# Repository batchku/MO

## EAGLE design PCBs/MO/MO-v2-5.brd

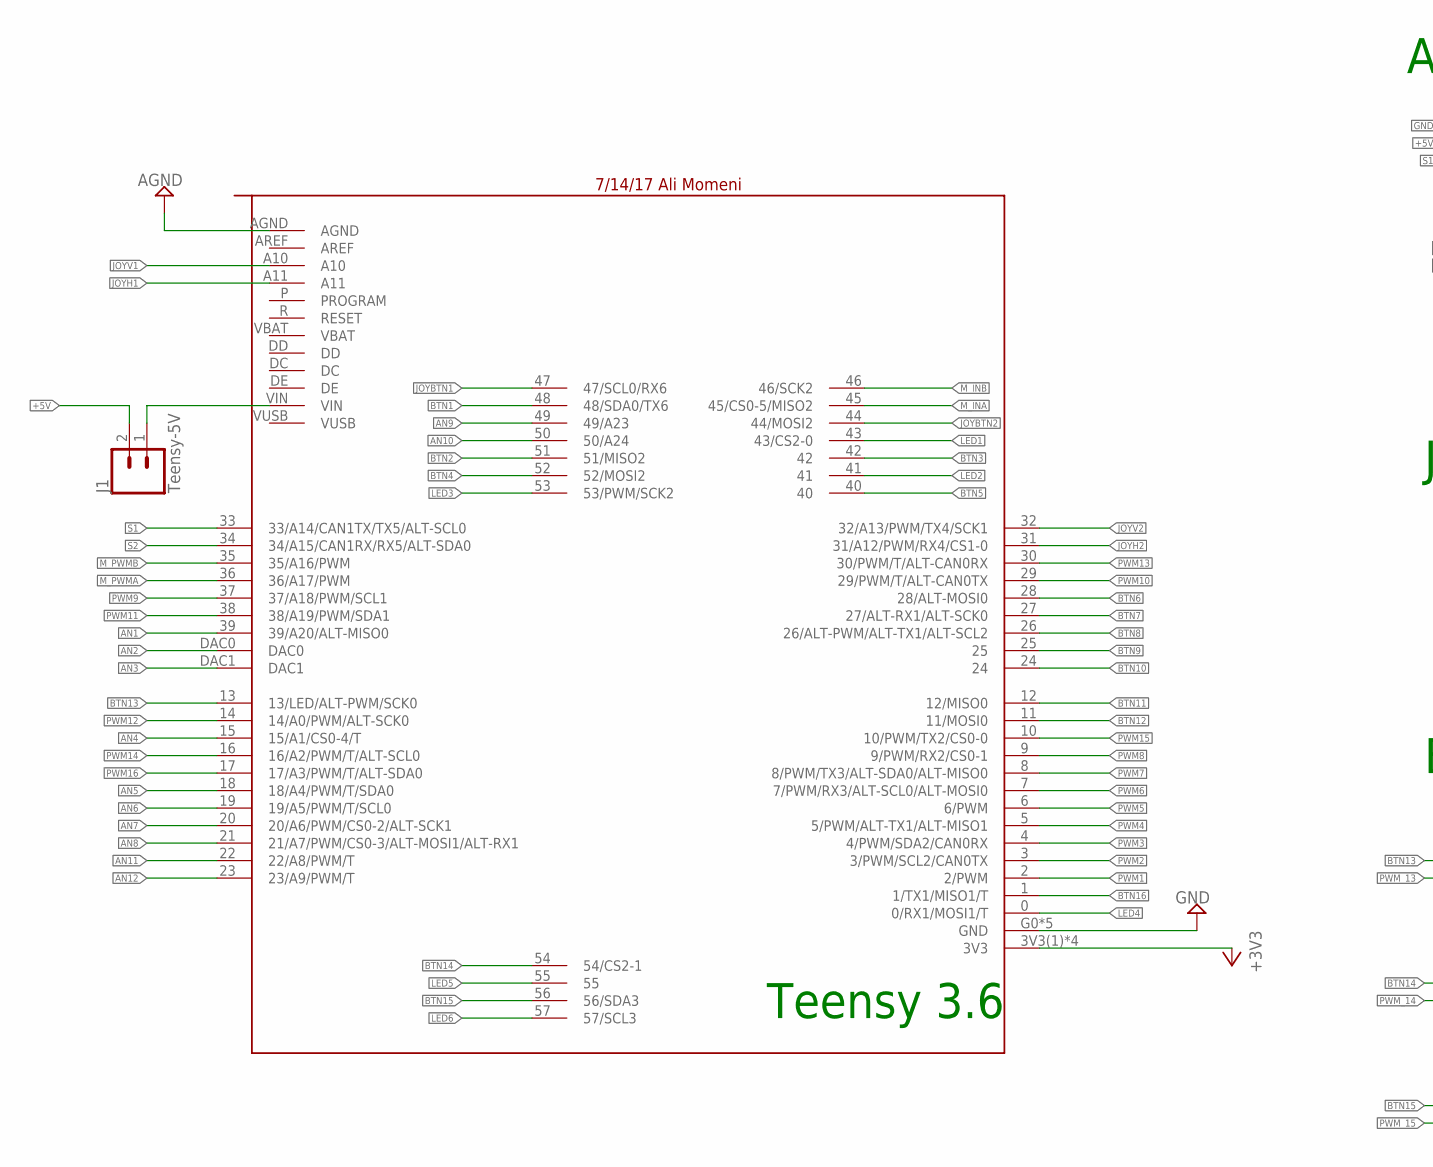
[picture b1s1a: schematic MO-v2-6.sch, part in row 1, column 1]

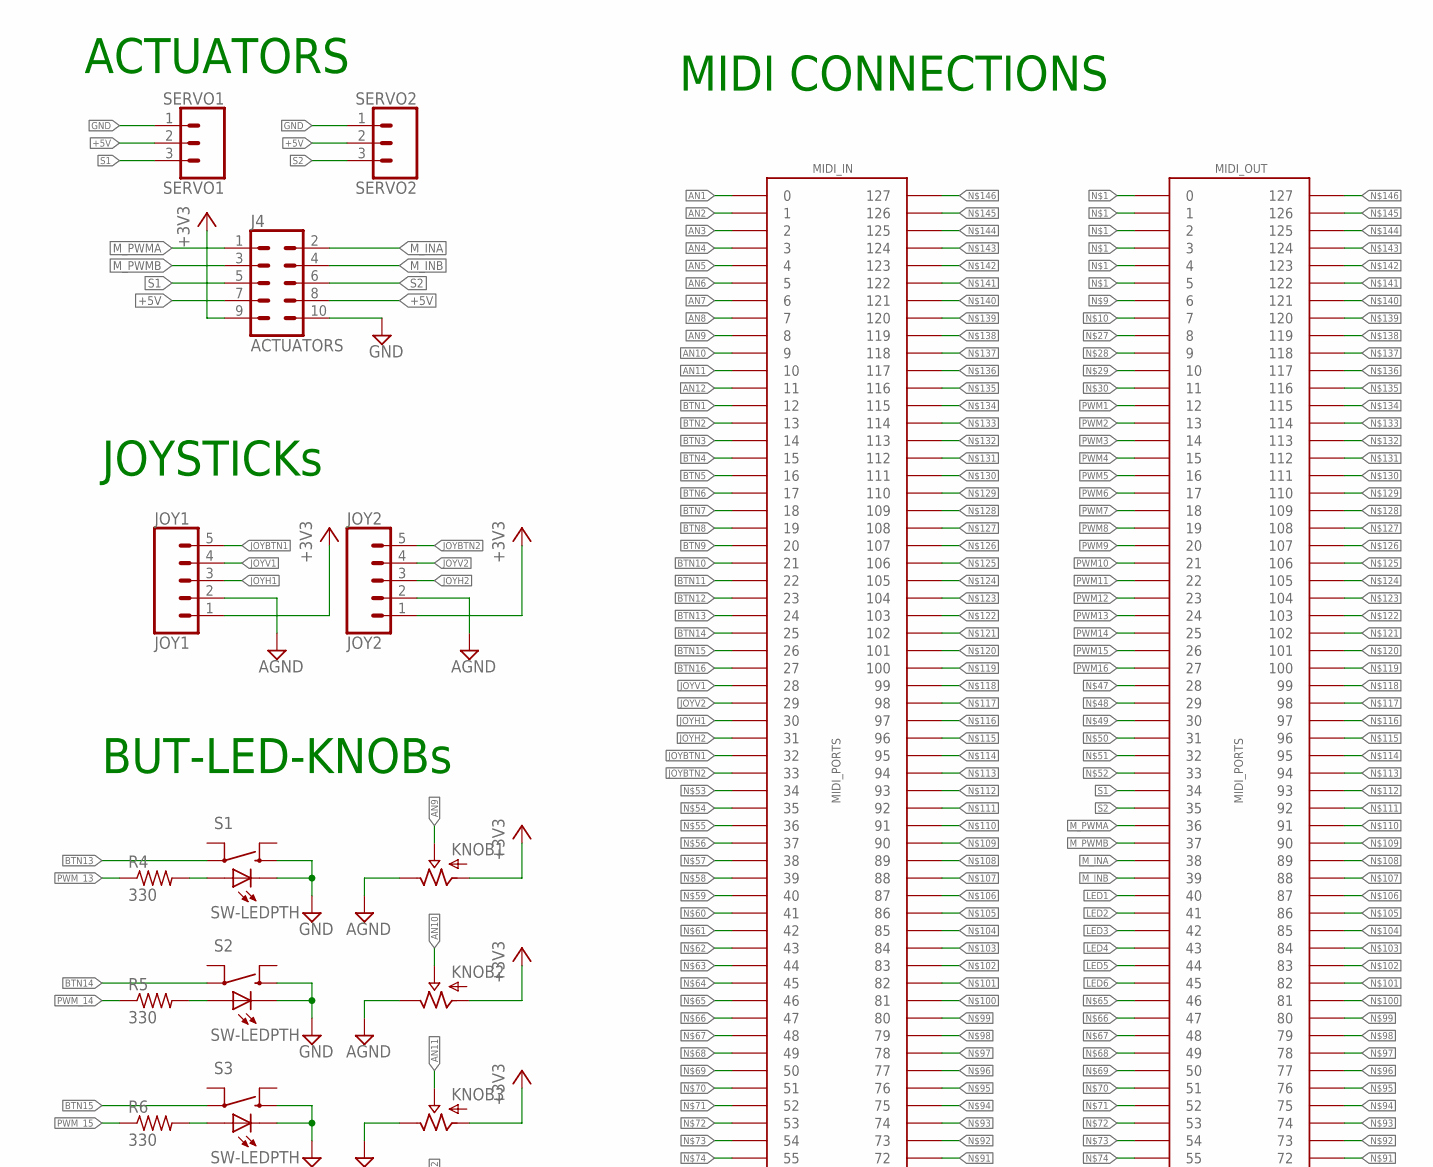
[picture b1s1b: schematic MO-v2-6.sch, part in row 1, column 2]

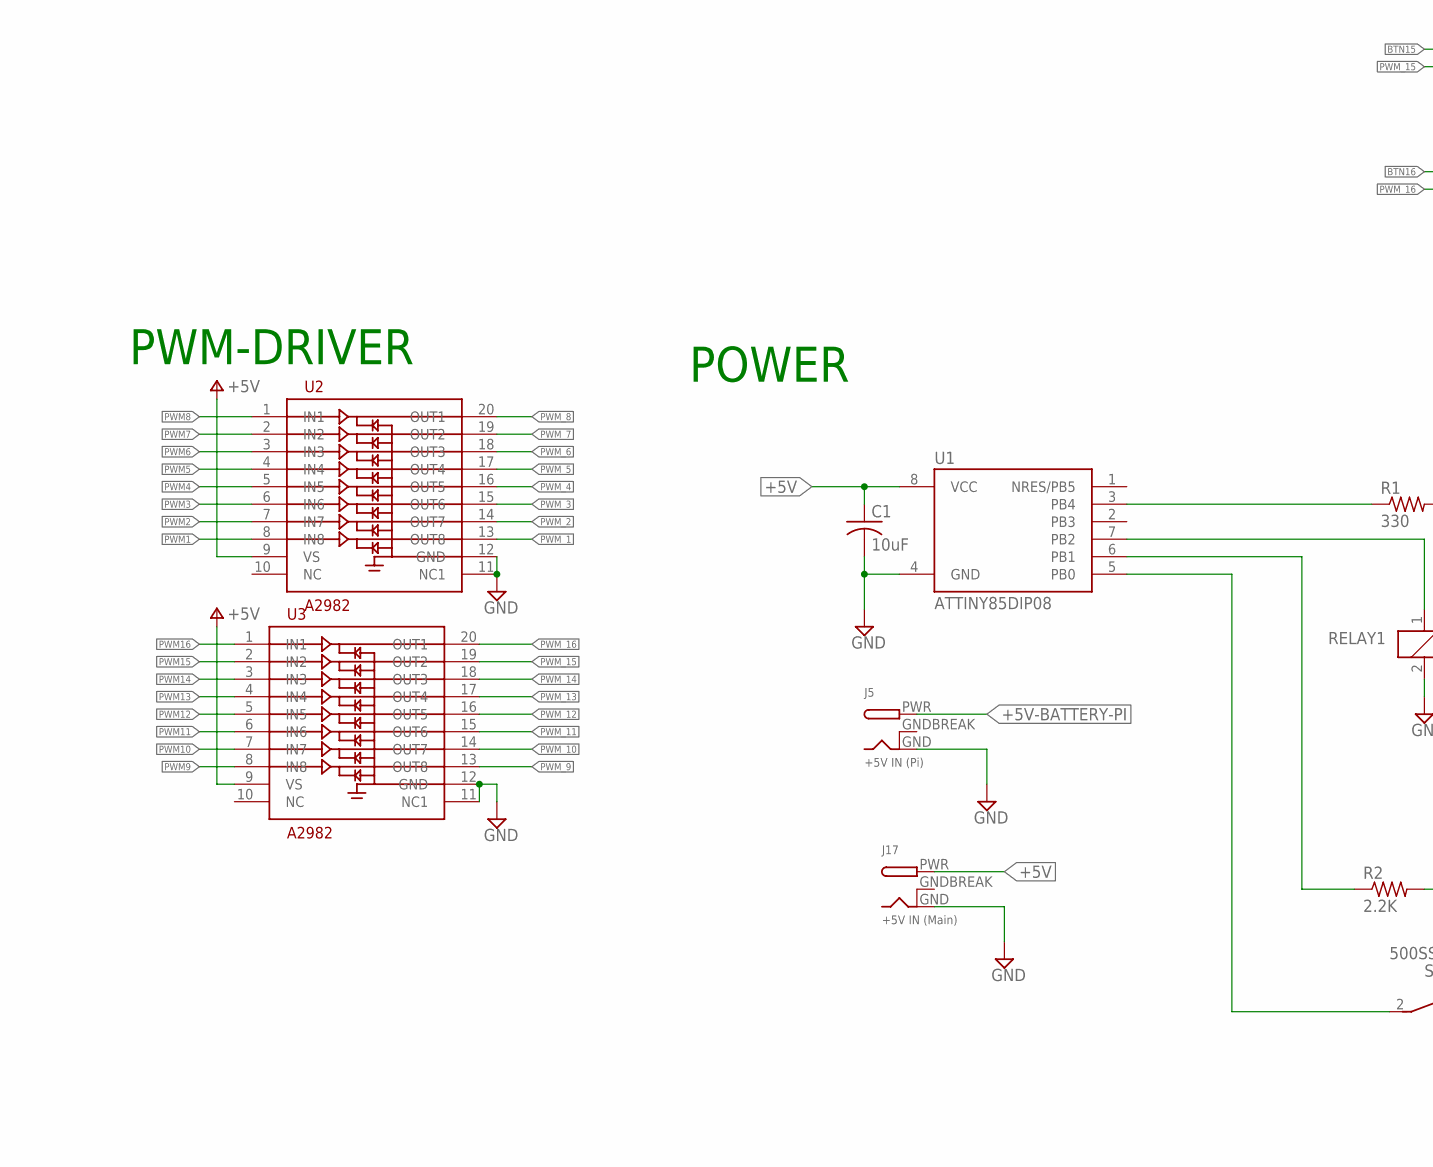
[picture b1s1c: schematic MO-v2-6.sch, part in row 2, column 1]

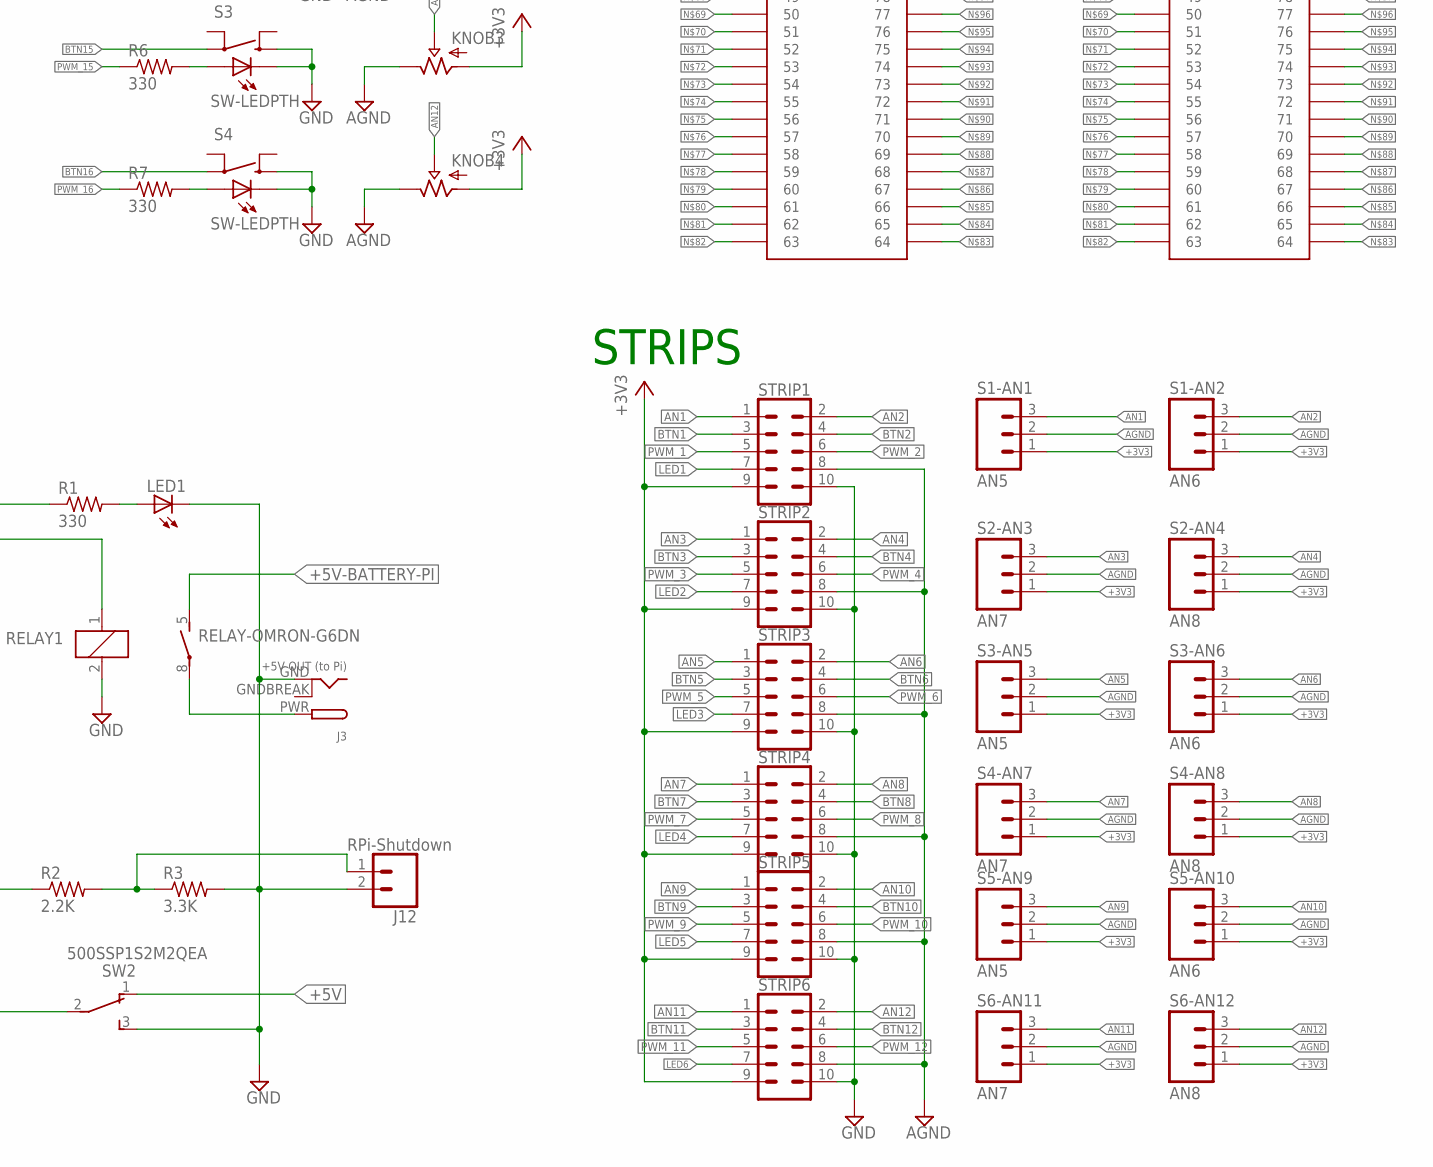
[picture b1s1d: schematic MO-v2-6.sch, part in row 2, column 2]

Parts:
C1: 10uF; C050-024X044
J1: Teensy-5V; 1X02_LOCK
J3: +5V OUT (to Pi); DCJACK_2MM_PTH
J4: ACTUATORS; 2X5-SHROUDED_LOCK
J5: +5V IN (Pi); DCJACK_2MM_PTH
J12: RPi-Shutdown; 1X02_LOCK
J17: +5V IN (Main); DCJACK_2MM_PTH
JOY1: JOY1; 1X05_LOCK
JOY2: JOY2; 1X05_LOCK
KNOB1, KNOB2, KNOB3, KNOB4: POTALPHA_RD901; POT_ALPHA_RD901F-40-(L)R1
LED1: LED3MM
R1, R4, R5, R6, R7: 330; 0204/7
R2: 2.2K; 0204/7
R3: 3.3K; 0204/7
RELAY1: RELAY-OMRON-G6DN; G6DN-1A
S1, S2, S3, S4: SW-LEDPTH; SWITCH_TR2-MOMENTARY-LED
S1-AN1, S3-AN5, S5-AN9: AN5; 1X03_LOCK
S1-AN2, S3-AN6, S5-AN10: AN6; 1X03_LOCK
S2-AN3, S4-AN7, S6-AN11: AN7; 1X03_LOCK
S2-AN4, S4-AN8, S6-AN12: AN8; 1X03_LOCK
SERVO1: SERVO1; 1X03_LOCK@1
SERVO2: SERVO2; 1X03_LOCK@1
STRIP1, STRIP2, STRIP3, STRIP4, STRIP5, STRIP6: CONN_05X2SHD_LOCK; 2X5-SHROUDED_LOCK
SW2: 500SSP1S2M2QEA; SWITCH_SPDT_500SSP1S2M2QEA
TEENSY: TEENSY3_6-ALI_NO-USB-HOST; TEENSY3-6_NO-USB-HOST
U1: ATTINY85DIP08; DIP08
U2, U3: A2982; SOIC20

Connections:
+3V3: J4.9, JOY1.1, JOY2.1, KNOB1.1 (IN), KNOB2.1 (IN), KNOB3.1 (IN), KNOB4.1 (IN), S1-AN1.1, S1-AN2.1, S2-AN3.1, S2-AN4.1, S3-AN5.1, S3-AN6.1, S4-AN7.1, S4-AN8.1, S5-AN9.1, S5-AN10.1, S6-AN11.1, S6-AN12.1, STRIP1.9, STRIP2.9, STRIP3.9, STRIP4.9, STRIP5.9, STRIP6.9, TEENSY.3V3(1) (3V3), TEENSY.3V3(2) (3V3), TEENSY.3V3(3) (3V3), TEENSY.3V3(4) (3V3); also elsewhere on the board
+5V: C1.1, J1.2, J4.7, J4.8, J17.PWR, SERVO1.2, SERVO2.2, SW2.1, U1.8 (VCC), U2.9 (VS), U3.9 (VS); also elsewhere on the board
+5V-BATTERY-PI: J5.PWR, RELAY1.5
AGND: JOY1.2, JOY2.2, KNOB1.3 (OUT), KNOB2.3 (OUT), KNOB3.3 (OUT), KNOB4.3 (OUT), S1-AN1.2, S1-AN2.2, S2-AN3.2, S2-AN4.2, S3-AN5.2, S3-AN6.2, S4-AN7.2, S4-AN8.2, S5-AN9.2, S5-AN10.2, S6-AN11.2, S6-AN12.2, STRIP1.8, STRIP2.8, STRIP3.8, STRIP4.8, STRIP5.8, STRIP6.8, TEENSY.AGND; also elsewhere on the board
AN1: S1-AN1.3, STRIP1.1, TEENSY.39 (39/A20/ALT-MISO0)
AN2: S1-AN2.3, STRIP1.2, TEENSY.DAC0
AN3: S2-AN3.3, STRIP2.1, TEENSY.DAC1
AN4: S2-AN4.3, STRIP2.2, TEENSY.15 (15/A1/CS0-4/T)
AN5: S3-AN5.3, STRIP3.1, TEENSY.18 (18/A4/PWM/T/SDA0)
AN6: S3-AN6.3, STRIP3.2, TEENSY.19 (19/A5/PWM/T/SCL0)
AN7: S4-AN7.3, STRIP4.1, TEENSY.20 (20/A6/PWM/CS0-2/ALT-SCK1)
AN8: S4-AN8.3, STRIP4.2, TEENSY.21 (21/A7/PWM/CS0-3/ALT-MOSI1/ALT-RX1)
AN9: KNOB1.2 (WIPER), S5-AN9.3, STRIP5.1, TEENSY.49 (49/A23); also elsewhere on the board
AN10: KNOB2.2 (WIPER), S5-AN10.3, STRIP5.2, TEENSY.50 (50/A24); also elsewhere on the board
AN11: KNOB3.2 (WIPER), S6-AN11.3, STRIP6.1, TEENSY.22 (22/A8/PWM/T); also elsewhere on the board
AN12: KNOB4.2 (WIPER), S6-AN12.3, STRIP6.2, TEENSY.23 (23/A9/PWM/T); also elsewhere on the board
BTN1: STRIP1.3, TEENSY.48 (48/SDA0/TX6)
BTN2: STRIP1.4, TEENSY.51 (51/MISO2)
BTN3: STRIP2.3, TEENSY.42
BTN4: STRIP2.4, TEENSY.52 (52/MOSI2)
BTN5: STRIP3.3, TEENSY.40
BTN6: STRIP3.4, TEENSY.28 (28/ALT-MOSI0)
BTN7: STRIP4.3, TEENSY.27 (27/ALT-RX1/ALT-SCK0)
BTN8: STRIP4.4, TEENSY.26 (26/ALT-PWM/ALT-TX1/ALT-SCL2)
BTN9: STRIP5.3, TEENSY.25
BTN10: STRIP5.4, TEENSY.24
BTN11: STRIP6.3, TEENSY.12 (12/MISO0)
BTN12: STRIP6.4, TEENSY.11 (11/MOSI0)
BTN13: S1.3, TEENSY.13 (13/LED/ALT-PWM/SCK0)
BTN14: S2.3, TEENSY.54 (54/CS2-1)
BTN15: S3.3, TEENSY.56 (56/SDA3)
BTN16: S4.3, TEENSY.1 (1/TX1/MISO1/T)
GND: C1.2, J3.GND, J4.10, J5.GND, J12.2, J17.GND, LED1.K (C), R3.2, RELAY1.2, S1.1, S1.C, S2.1, S2.C, S3.1, S3.C, S4.1, S4.C, SERVO1.1, SERVO2.1, STRIP1.10, STRIP2.10, STRIP3.10, STRIP4.10, STRIP5.10, STRIP6.10, SW2.3, TEENSY.G0 (GND), TEENSY.G1 (GND), TEENSY.G2 (GND), TEENSY.G3 (GND), TEENSY.G6 (GND), U1.4 (GND), U2.11 (NC1), U2.12 (GND), U3.11 (NC1), U3.12 (GND); also elsewhere on the board
GNDBREAK: J3.GNDBREAK, J5.GNDBREAK, J17.GNDBREAK
JOYB1: JOY1.5, TEENSY.47 (47/SCL0/RX6)
JOYB2: JOY2.5, TEENSY.44 (44/MOSI2)
JOYH1: JOY1.3, TEENSY.A11
JOYH2: JOY2.3, TEENSY.31 (31/A12/PWM/RX4/CS1-0)
JOYV1: JOY1.4, TEENSY.A10
JOYV2: JOY2.4, TEENSY.32 (32/A13/PWM/TX4/SCK1)
LED1: STRIP1.7, TEENSY.43 (43/CS2-0)
LED2: STRIP2.7, TEENSY.41
LED3: STRIP3.7, TEENSY.53 (53/PWM/SCK2)
LED4: STRIP4.7, TEENSY.0 (0/RX1/MOSI1/T)
LED5: STRIP5.7, TEENSY.55
LED6: STRIP6.7, TEENSY.57 (57/SCL3)
M_INA: J4.2, TEENSY.45 (45/CS0-5/MISO2)
M_INB: J4.4, TEENSY.46 (46/SCK2)
M_PWMA: J4.1, TEENSY.36 (36/A17/PWM)
M_PWMB: J4.3, TEENSY.35 (35/A16/PWM)
unnamed: LED1.A, R1.2
unnamed: R4.2, S1.A
unnamed: R5.2, S2.A
unnamed: J12.1, R2.2, R3.1
unnamed: R6.2, S3.A
unnamed: J1.1, TEENSY.VIN
unnamed: R7.2, S4.A
PI-REST: R2.1, U1.6 (PB1)
PWM1: TEENSY.2 (2/PWM), U2.8 (IN8)
PWM2: TEENSY.3 (3/PWM/SCL2/CAN0TX), U2.7 (IN7)
PWM3: TEENSY.4 (4/PWM/SDA2/CAN0RX), U2.6 (IN6)
PWM4: TEENSY.5 (5/PWM/ALT-TX1/ALT-MISO1), U2.5 (IN5)
PWM5: TEENSY.6 (6/PWM), U2.4 (IN4)
PWM6: TEENSY.7 (7/PWM/RX3/ALT-SCL0/ALT-MOSI0), U2.3 (IN3)
PWM7: TEENSY.8 (8/PWM/TX3/ALT-SDA0/ALT-MISO0), U2.2 (IN2)
PWM8: TEENSY.9 (9/PWM/RX2/CS0-1), U2.1 (IN1)
PWM9: TEENSY.37 (37/A18/PWM/SCL1), U3.8 (IN8); also elsewhere on the board
PWM10: TEENSY.29 (29/PWM/T/ALT-CAN0TX), U3.7 (IN7); also elsewhere on the board
PWM11: TEENSY.38 (38/A19/PWM/SDA1), U3.6 (IN6); also elsewhere on the board
PWM12: TEENSY.14 (14/A0/PWM/ALT-SCK0), U3.5 (IN5); also elsewhere on the board
PWM13: TEENSY.30 (30/PWM/T/ALT-CAN0RX), U3.4 (IN4); also elsewhere on the board
PWM14: TEENSY.16 (16/A2/PWM/T/ALT-SCL0), U3.3 (IN3); also elsewhere on the board
PWM15: TEENSY.10 (10/PWM/TX2/CS0-0), U3.2 (IN2); also elsewhere on the board
PWM16: TEENSY.17 (17/A3/PWM/T/ALT-SDA0), U3.1 (IN1); also elsewhere on the board
PWM_1: STRIP1.5, U2.13 (OUT8)
PWM_2: STRIP1.6, U2.14 (OUT7)
PWM_3: STRIP2.5, U2.15 (OUT6)
PWM_4: STRIP2.6, U2.16 (OUT5)
PWM_5: STRIP3.5, U2.17 (OUT4)
PWM_6: STRIP3.6, U2.18 (OUT3)
PWM_7: STRIP4.5, U2.19 (OUT2)
PWM_8: STRIP4.6, U2.20 (OUT1)
PWM_9: STRIP5.5, U3.13 (OUT8); also elsewhere on the board
PWM_10: STRIP5.6, U3.14 (OUT7); also elsewhere on the board
PWM_11: STRIP6.5, U3.15 (OUT6); also elsewhere on the board
PWM_12: STRIP6.6, U3.16 (OUT5); also elsewhere on the board
PWM_13: R4.1, U3.17 (OUT4); also elsewhere on the board
PWM_14: R5.1, U3.18 (OUT3); also elsewhere on the board
PWM_15: R6.1, U3.19 (OUT2); also elsewhere on the board
PWM_16: R7.1, U3.20 (OUT1); also elsewhere on the board
RELAY-PWR: J3.PWR, RELAY1.8
S1: J4.5, SERVO1.3, TEENSY.33 (33/A14/CAN1TX/TX5/ALT-SCL0)
S2: J4.6, SERVO2.3, TEENSY.34 (34/A15/CAN1RX/RX5/ALT-SDA0)
TINY_LED: R1.1, U1.3 (PB4)
TINY_RELAY: RELAY1.1, U1.7 (PB2)
TINY_SWITCH: SW2.2, U1.5 (PB0)

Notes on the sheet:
BUT-LED-KNOBs
JOYSTICKs
PWM-DRIVER
STRIPS
ACTUATORS
POWER
Teensy 3.6
MIDI CONNECTIONS

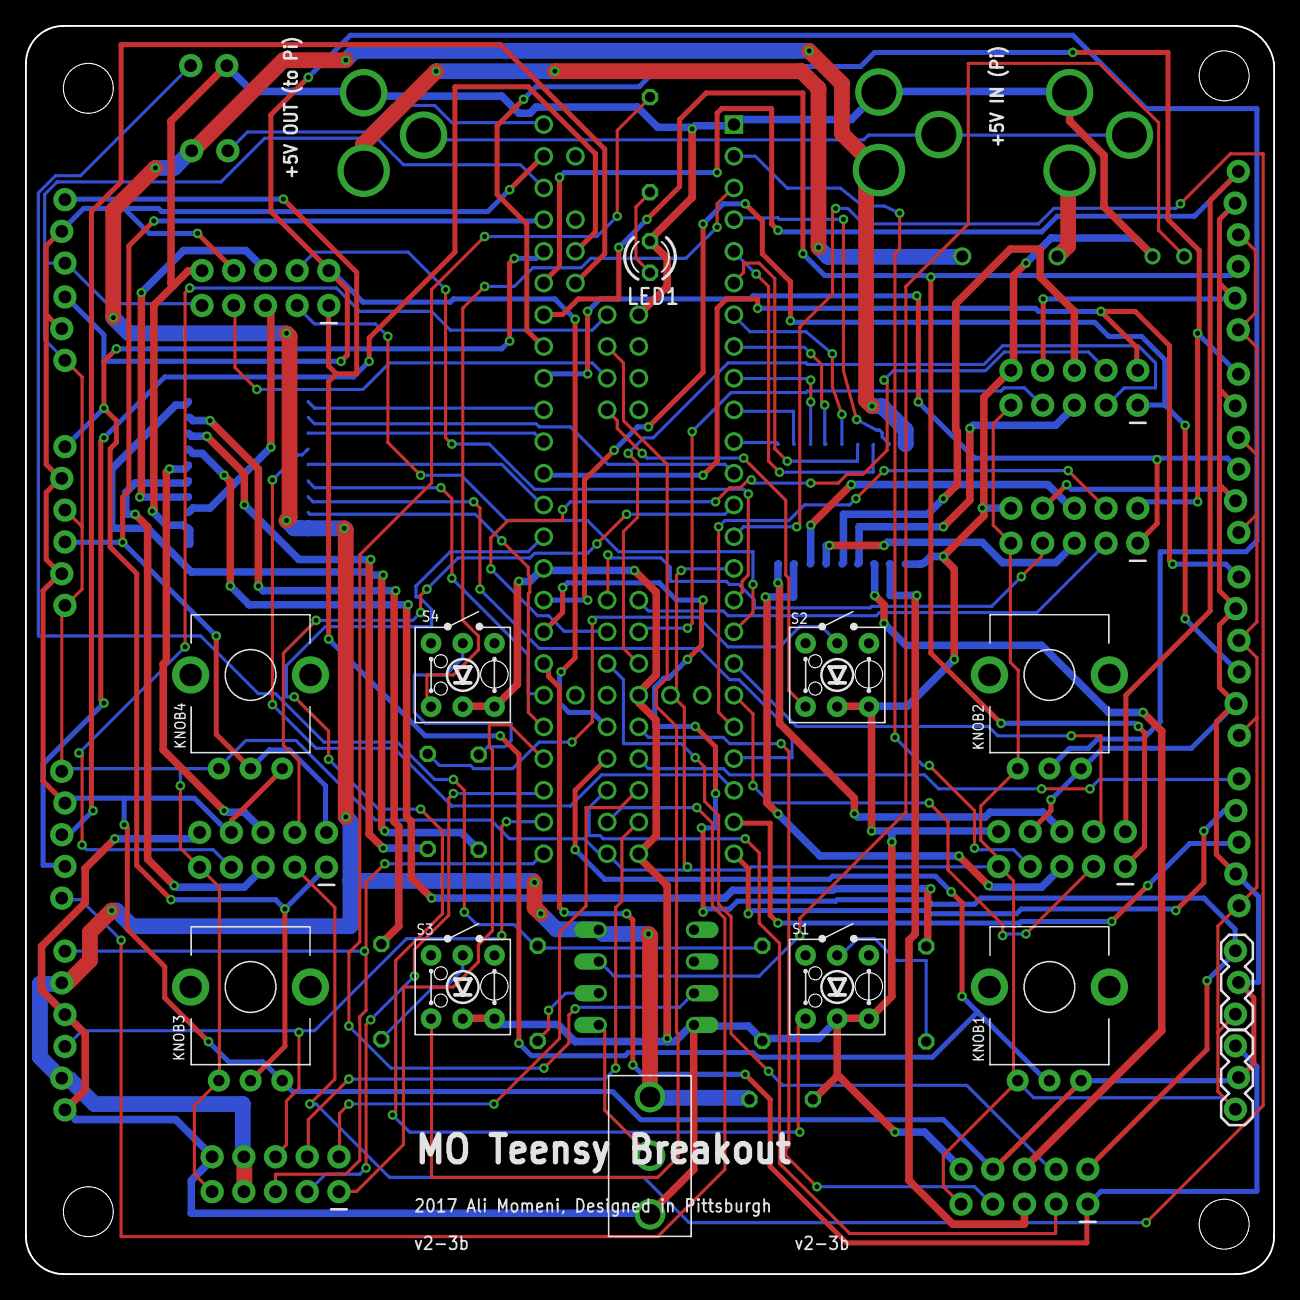
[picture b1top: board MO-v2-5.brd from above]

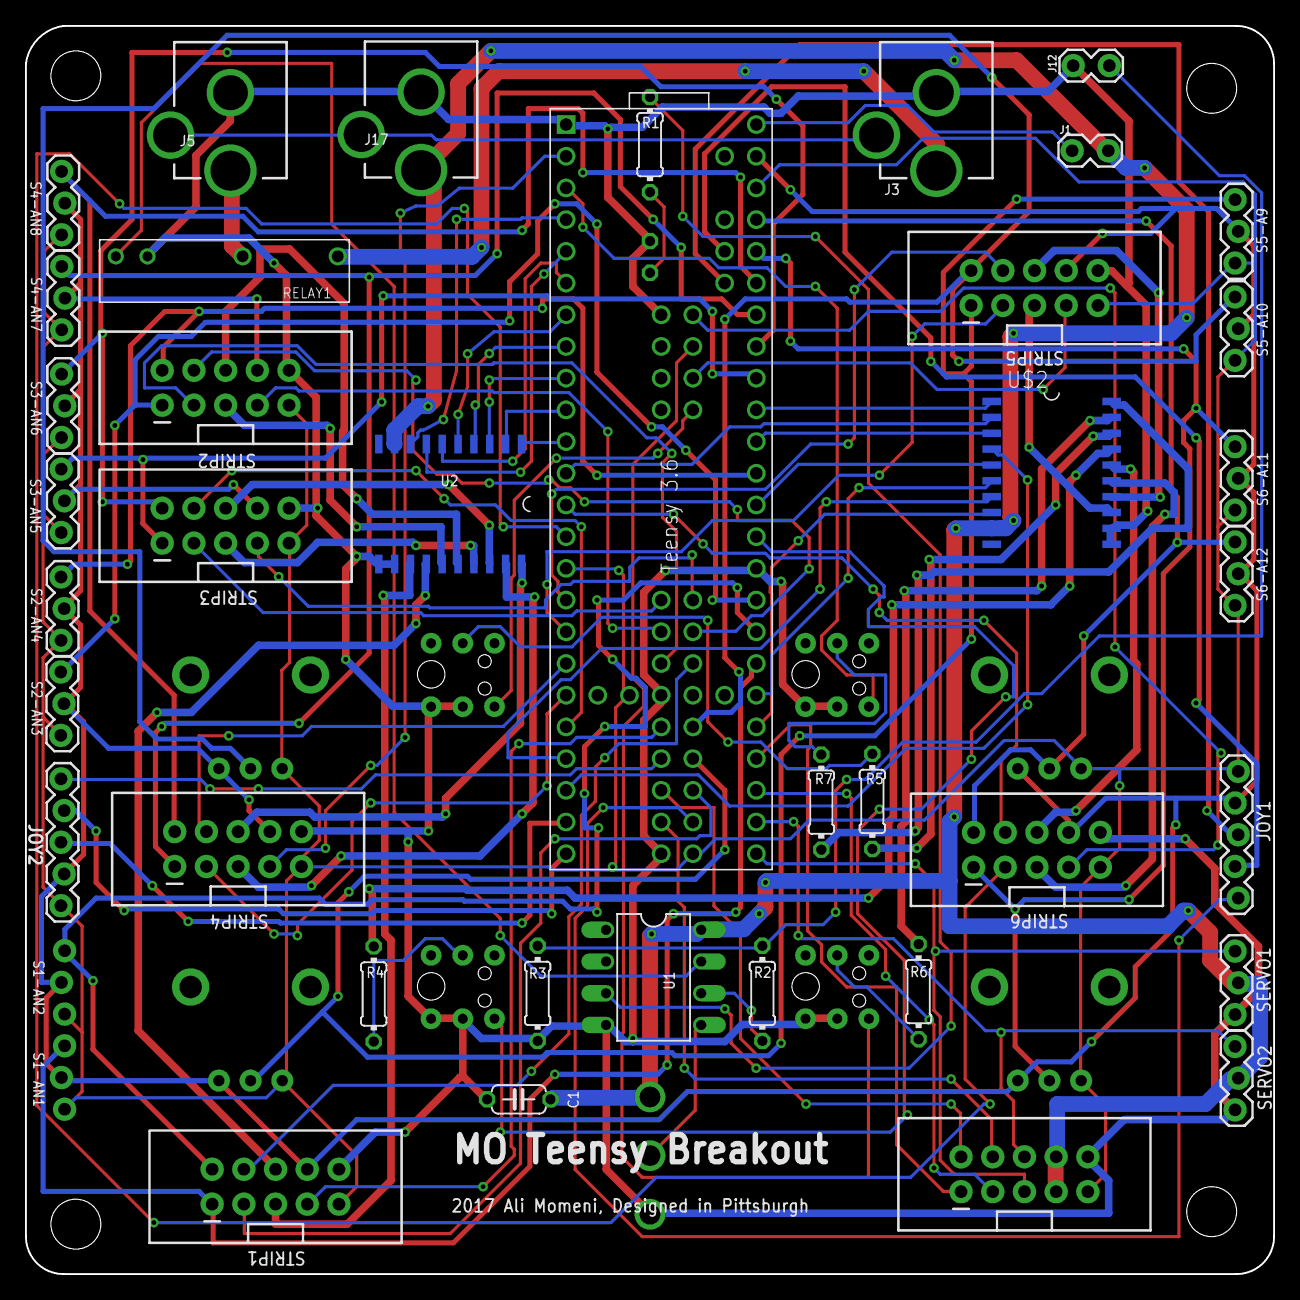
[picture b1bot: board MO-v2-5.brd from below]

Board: 2 copper layers, 100.0 x 100.0 mm, 51 parts (39 on the bottom side), 96 nets.

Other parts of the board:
S5-A9: AN5; 1X03_LOCK
S5-A10: AN6; 1X03_LOCK
S6-A11: AN7; 1X03_LOCK
S6-A12: AN8; 1X03_LOCK
U$2: A2982; SOIC20

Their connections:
+3V3: S5-A9.1, S5-A10.1, S6-A11.1, S6-A12.1; also elsewhere on the board
+5V: U$2.9; also elsewhere on the board
AGND: S5-A9.2, S5-A10.2, S6-A11.2, S6-A12.2; also elsewhere on the board
AN9: S5-A9.3; also elsewhere on the board
AN10: S5-A10.3; also elsewhere on the board
AN11: S6-A11.3; also elsewhere on the board
AN12: S6-A12.3; also elsewhere on the board
GND: U$2.11, U$2.12; also elsewhere on the board
PWM9: U$2.8; also elsewhere on the board
PWM10: U$2.7; also elsewhere on the board
PWM11: U$2.6; also elsewhere on the board
PWM12: U$2.5; also elsewhere on the board
PWM13: U$2.4; also elsewhere on the board
PWM14: U$2.3; also elsewhere on the board
PWM15: U$2.2; also elsewhere on the board
PWM16: U$2.1; also elsewhere on the board
PWM_9: U$2.13; also elsewhere on the board
PWM_10: U$2.14; also elsewhere on the board
PWM_11: U$2.15; also elsewhere on the board
PWM_12: U$2.16; also elsewhere on the board
PWM_13: U$2.17; also elsewhere on the board
PWM_14: U$2.18; also elsewhere on the board
PWM_15: U$2.19; also elsewhere on the board
PWM_16: U$2.20; also elsewhere on the board

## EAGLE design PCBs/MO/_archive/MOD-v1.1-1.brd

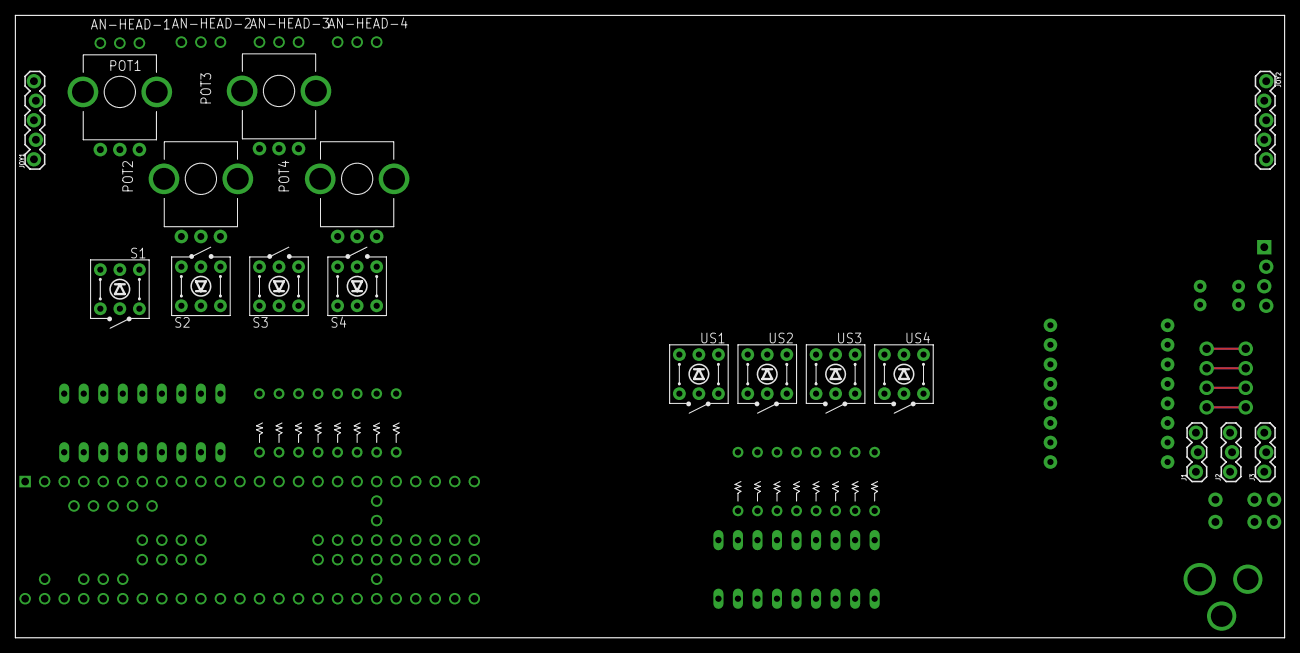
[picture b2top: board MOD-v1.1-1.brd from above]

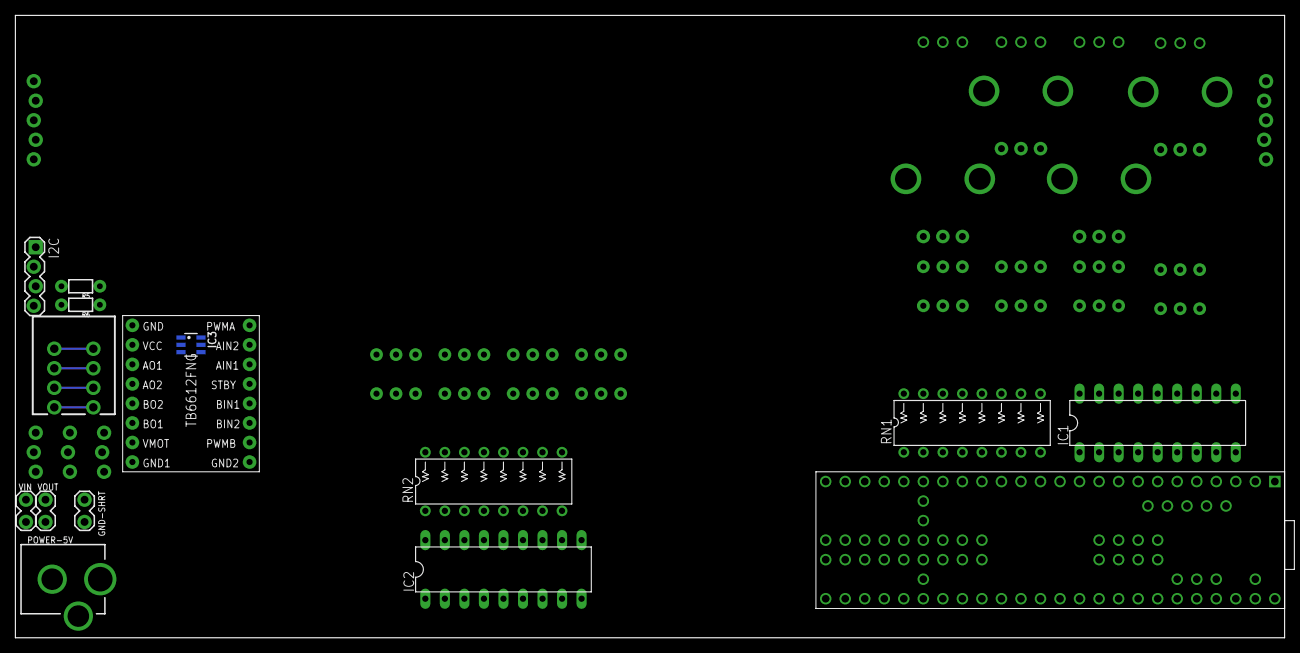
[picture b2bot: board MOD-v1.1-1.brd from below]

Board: 2 copper layers, 165.1 x 81.0 mm, 36 parts (15 on the bottom side), 80 nets, no tracks yet.

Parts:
AN-HEAD-1, AN-HEAD-2, AN-HEAD-3, AN-HEAD-4: 1X03_NO_SILK
GND-SHRT: 1X02_LOCK
I2C: 1X04_LOCK
IC1, IC2: ULN2803; DIL18
IC3: SN74LVC2G04DBV; SOT23-6
J1: SERVO 1; 1X03_LOCK@1
J2: SERVO 2; 1X03_LOCK@1
J3: SERVO 3; 1X03_LOCK@1
JOY1, JOY2: 1X05_LOCK
MOTORS1: SPRINGTERMINAL-2.54MM-4
POT1, POT2, POT3, POT4: TRIM-PCB-9MM
POWER-5V: DCJACK_2MM_PTH
R5, R6: 1/6W-RES
RN1, RN2: 330; RESISTOR-NET-8P-DIL16
S1, S2, S3, S4: SW-LEDPTH; TR2-SWITCH-MOMENTARY-LED
TEENSY: TEENSY3_6--ALLPINS; T36
U$7: POLOLU_TB6612FNG
US1, US2, US3, US4: SW-LEDPTH; TR2-SWITCH-MOMENTARY-LED
VIN: 1X02_LOCK
VOUT: 1X02_LOCK

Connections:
+3V3: AN-HEAD-1.1, AN-HEAD-2.1, AN-HEAD-3.1, AN-HEAD-4.1, I2C.1, IC3.5, JOY1.2, JOY2.2, POT1.1, POT2.1, POT3.1, POT4.1, R5.1, R6.1, TEENSY.3V3(1), TEENSY.3V3(2), TEENSY.3V3(3), TEENSY.3V3(4), U$7.STBY, U$7.VCC
+5V: IC1.10, IC2.10, J1.2, J2.2, J3.2, POWER-5V.PWR, VIN.1
AGND: AN-HEAD-1.3, AN-HEAD-2.3, AN-HEAD-3.3, AN-HEAD-4.3, JOY1.1, JOY2.1, POT1.3, POT2.3, POT3.3, POT4.3, TEENSY.AGND
AN1: AN-HEAD-1.2, POT1.2, TEENSY.14
AN2: AN-HEAD-2.2, POT2.2, TEENSY.15
AN3: AN-HEAD-3.2, POT3.2, TEENSY.16
AN4: AN-HEAD-4.2, POT4.2, TEENSY.33
B1: S1.1, TEENSY.11
B2: S2.1, TEENSY.12
B3: S3.1, TEENSY.24
B4: S4.1, TEENSY.25
GND: GND-SHRT.2, I2C.2, IC1.9, IC2.9, IC3.2, J1.1, J2.1, J3.1, S1.3, S2.3, S3.3, S4.3, TEENSY.G0, TEENSY.G1, TEENSY.G2, TEENSY.G3, TEENSY.G4, TEENSY.G5, TEENSY.G6, U$7.GND, US1.3, US2.3, US3.3, US4.3, VIN.2, VOUT.2
GND_MOT: GND-SHRT.1, POWER-5V.GND, U$7.GND1, U$7.GND2
I2C_SCL: I2C.3, R5.2
I2C_SDA: I2C.4, R6.2
JOYB1: JOY1.5, TEENSY.1
JOYB2: JOY2.5, TEENSY.0
JOYH1: JOY1.3, TEENSY.20
JOYH2: JOY2.3, TEENSY.18
JOYV1: JOY1.4, TEENSY.19
JOYV2: JOY2.4, TEENSY.17
L1: IC1.8, TEENSY.2
L2: IC1.7, TEENSY.3
L3: IC1.6, TEENSY.4
L4: IC1.5, TEENSY.5
L5: IC1.4, TEENSY.6
L6: IC1.3, TEENSY.7
L7: IC1.2, TEENSY.8
L8: IC1.1, TEENSY.23
L9: IC2.8, TEENSY.29
L10: IC2.7, TEENSY.30
L11: IC2.6, TEENSY.31
L12: IC2.5, TEENSY.32
LED1: RN1.H2, S1.C
LED2: RN1.G2, S2.C
LED3: RN1.F2, S3.C
LED4: RN1.E2, S4.C
M_AIN: IC3.3, TEENSY.40, U$7.AIN1
M_BIN: IC3.1, TEENSY.41, U$7.BIN2
M_PWMA: TEENSY.21, U$7.PWMA
M_PWMB: TEENSY.22, U$7.PWMB
unnamed: IC3.6, U$7.BIN1
unnamed: IC3.4, U$7.AIN2
unnamed: IC1.18, RN1.A1
unnamed: IC1.17, RN1.B1
unnamed: IC1.16, RN1.C1
unnamed: IC1.15, RN1.D1
unnamed: IC1.14, RN1.E1
unnamed: IC1.13, RN1.F1
unnamed: IC1.12, RN1.G1
unnamed: IC1.11, RN1.H1
unnamed: IC2.18, RN2.A1
unnamed: IC2.17, RN2.B1
unnamed: IC2.16, RN2.C1
unnamed: IC2.15, RN2.D1
unnamed: IC2.14, RN2.E1
unnamed: IC2.12, RN2.G1
unnamed: IC2.11, RN2.H1
unnamed: IC2.13, RN2.F1
unnamed: MOTORS1.P$1, U$7.BO1
unnamed: MOTORS1.P$2, U$7.BO2
unnamed: MOTORS1.P$3, U$7.AO2
unnamed: MOTORS1.P$4, U$7.AO1
S1: J1.3, TEENSY.9
S2: J2.3, TEENSY.10
S3: J3.3, TEENSY.49
UB1: TEENSY.57, US1.1
UB2: TEENSY.56, US2.1
UB3: TEENSY.55, US3.1
UB4: TEENSY.54, US4.1
UL1: IC2.4, TEENSY.53
UL2: IC2.3, TEENSY.52
UL3: IC2.2, TEENSY.51
UL4: IC2.1, TEENSY.50
ULED1: RN2.D2, US1.C
ULED2: RN2.C2, US2.C
ULED3: RN2.B2, US3.C
ULED4: RN2.A2, US4.C
V+: S1.A, S2.A, S3.A, S4.A, US1.A, US2.A, US3.A, US4.A
VMOT: U$7.VMOT, VOUT.1

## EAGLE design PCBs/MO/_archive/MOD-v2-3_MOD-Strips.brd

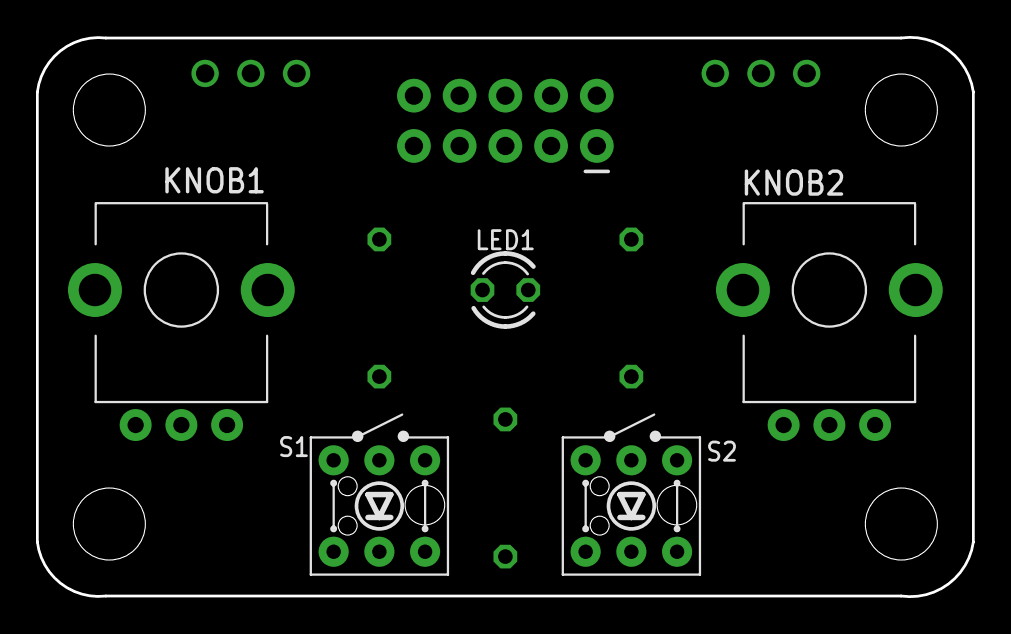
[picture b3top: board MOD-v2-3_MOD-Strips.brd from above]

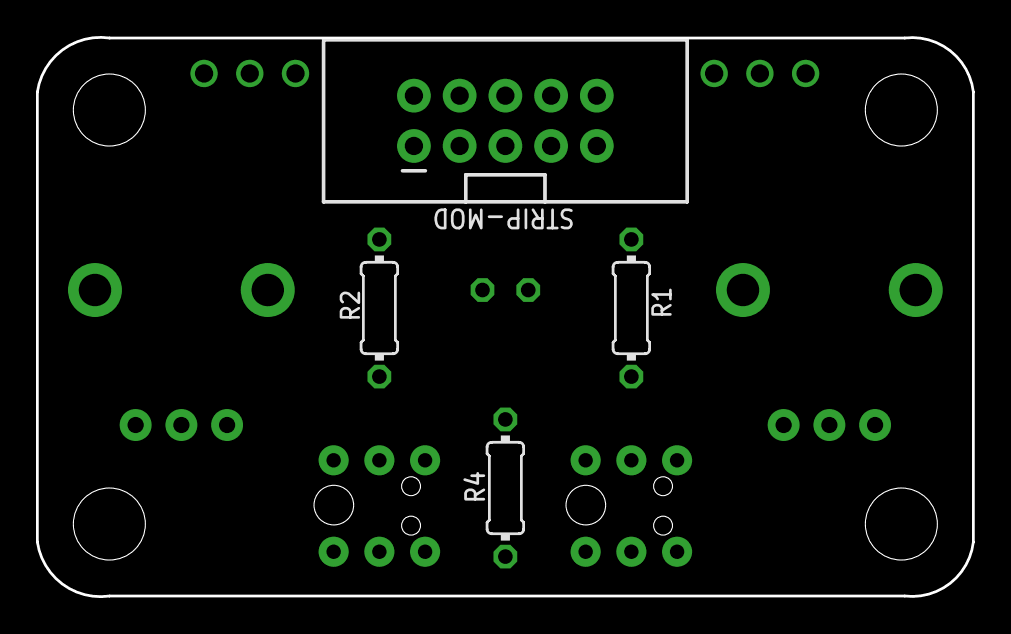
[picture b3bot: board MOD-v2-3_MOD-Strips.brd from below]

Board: 2 copper layers, 52.0 x 31.1 mm, 11 parts (6 on the bottom side), 13 nets, no tracks yet.

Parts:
AN-IN-1, AN-IN-2: 1X03_NO_SILK
KNOB1, KNOB2: POT_ALPHA_RD901F-40-(L)R1
LED1: LED3MM
R1, R2: 330; 0204/7
R4: 220; 0204/7
S1, S2: SW-LEDPTH; SWITCH_TR2-MOMENTARY-LED
STRIP-MOD: J1; 2X5-SHROUDED_LOCK

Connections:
+3V3: AN-IN-1.1, AN-IN-2.1, KNOB1.1, KNOB2.1, STRIP-MOD.9
AGND: AN-IN-1.3, AN-IN-2.3, KNOB1.3, KNOB2.3, STRIP-MOD.8
AN1: AN-IN-1.2, KNOB1.2, STRIP-MOD.1
AN2: AN-IN-2.2, KNOB2.2, STRIP-MOD.2
B1: S1.3, STRIP-MOD.3
B2: S2.3, STRIP-MOD.4
GND: LED1.K, S1.1, S1.C, S2.1, S2.C, STRIP-MOD.10
LED1: R4.1, STRIP-MOD.7
N1: LED1.A, R4.2
unnamed: R1.1, S1.A
unnamed: R2.1, S2.A
PWM_1: R1.2, STRIP-MOD.5
PWM_2: R2.2, STRIP-MOD.6

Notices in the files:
parts and their libraries:
SparkFun-Connectors: Licensing: Creative Commons ShareAlike 4.0 International - https://creativecommons.org/licenses/by-sa/4.0
74LV: Copyright (C) 2008, Bob Starr
